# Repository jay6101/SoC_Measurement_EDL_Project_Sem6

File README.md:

# EE 344 EDL Project
Topic - SoC Measurement using Coulomb Counting Method

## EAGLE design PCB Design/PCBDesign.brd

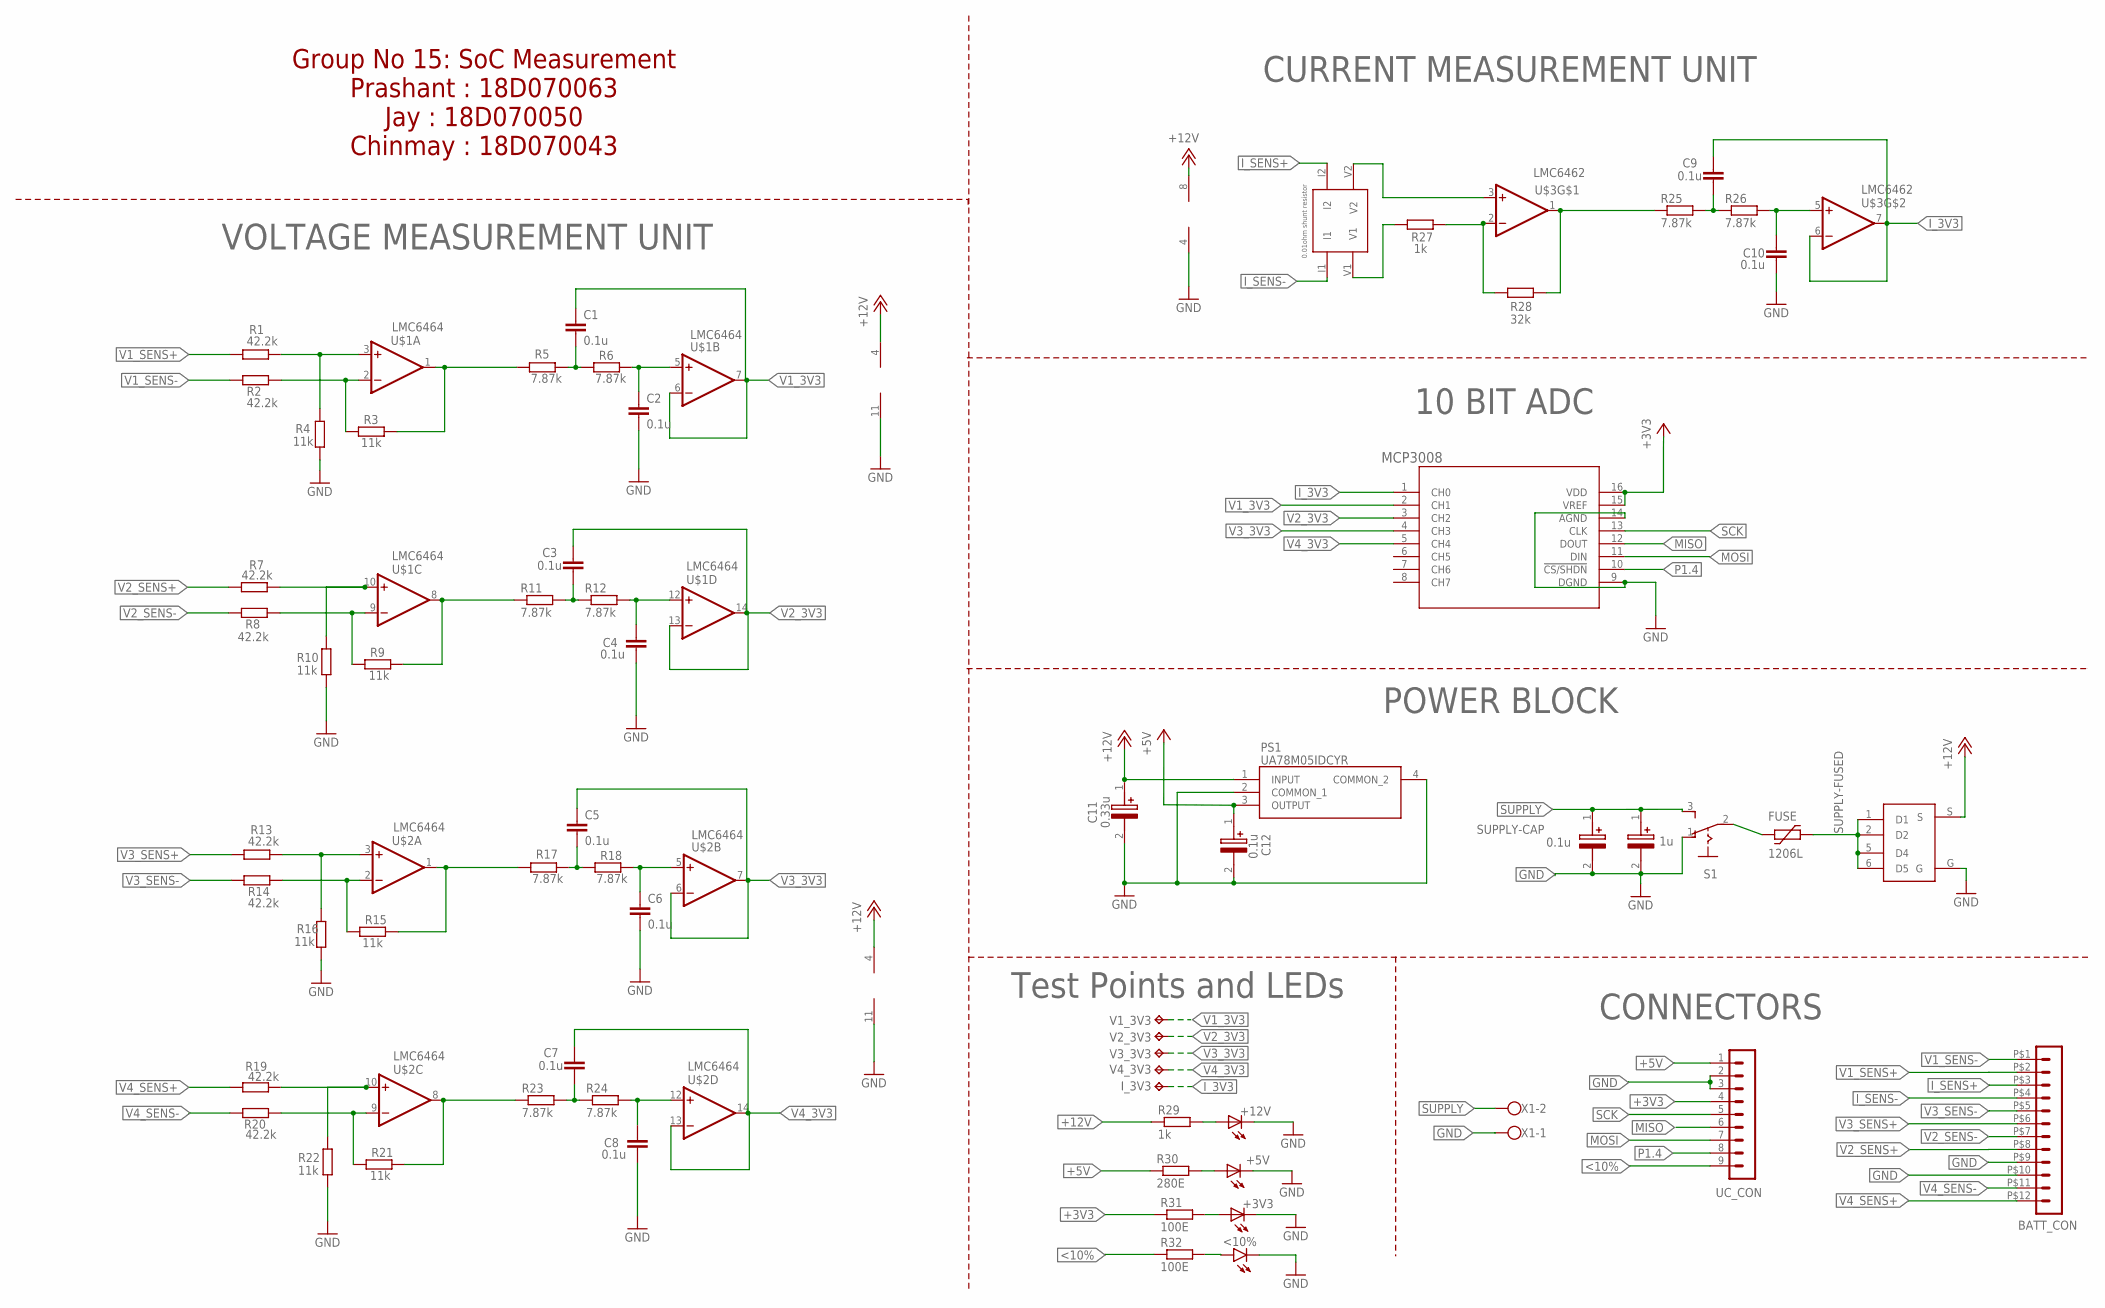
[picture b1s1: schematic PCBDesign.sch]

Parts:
+3V3, +5V, +12V: LED-FKIT-1206; FKIT-LED-1206
<10%: LED5MM
BATT_CON: HEADER_POS12_43045-1212; 43045-1212
C1, C2, C3, C4, C5, C6, C7, C8, C9, C10: 0.1u; C0805
C11: 0.33u; CAPPM2014X120N
C12: 0.1u; CAPPM2014X120N
FUSE: 1206L
I_3V3: TESTPADPAD1-13; P1-13
PS1: UA78M05IDCYR; SOT230P700X180-4N
R1, R2, R7, R8, R13, R14, R19, R20: 42.2k; R0805
R3, R4, R9, R10, R15, R16, R21, R22: 11k; R0805
R5, R6, R11, R12, R17, R18, R23, R24, R25, R26: 7.87k; R0805
R27, R29: 1k; R0805
R28: 32k; R0805
R30: 280E; R0805
R31, R32: 100E; R0805
S1: STS121PC04
S2: DMP3125L/SQ3419AEEV
SUPPLY-CAP: 1u; CAPPM2014X120N
SUPPLY-CAP1: 0.1u; CAPPM2014X120N
U1: MCP3008; SOIC16-N_MC_MCH-L
U$1, U$2: LMC6464; SO14_LONGPADS
U$3: LMC6462; S08
U$4: 0.01E; SHNT_R_0.01
UC_CON: MA09-1
V1_3V3, V2_3V3, V3_3V3, V4_3V3: TESTPADPAD1-13; P1-13
X1: W237-102

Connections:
+3V3: R31.1, U1.15 (VREF), U1.16 (VDD), UC_CON.4
+5V: C12.1 (+), PS1.3 (OUTPUT), R30.1, UC_CON.1
+12V: C11.1 (+), PS1.1 (INPUT), R29.1, S2.S, U$1.4 (V+), U$2.4 (V+), U$3.8 (V+)
<10%: R32.1, UC_CON.9
GND: +3V3.C, +5V.C, +12V.C, <10%.K (C), BATT_CON.P$9 (9), BATT_CON.P$10 (10), C2.2, C4.2, C6.2, C8.2, C10.2, C11.2 (-), C12.2 (-), PS1.2 (COMMON_1), PS1.4 (COMMON_2), R4.2, R10.2, R16.2, R22.2, S1.1 (O), S2.G, SUPPLY-CAP.2 (-), SUPPLY-CAP1.2 (-), U1.9 (DGND), U1.14 (AGND), U$1.11 (V-), U$2.11 (V-), U$3.4 (V-), UC_CON.2, UC_CON.3, X1.1
I_3V3: C9.1, I_3V3.TP, U1.1 (CH0), U$3.6 (-IN), U$3.7 (OUT)
I_SENS+: BATT_CON.P$3 (3), U$4.I2
I_SENS-: BATT_CON.P$4 (4), U$4.I1
MISO: U1.12 (DOUT), UC_CON.6
MOSI: U1.11 (DIN), UC_CON.7
unnamed: C1.2, R5.2, R6.1
unnamed: R1.2, R4.1, U$1.3 (+IN)
unnamed: R2.2, R3.1, U$1.2 (-IN)
unnamed: R3.2, R5.1, U$1.1 (OUT)
unnamed: FUSE.P$1 (1), S1.2
unnamed: +5V.A, R30.2
unnamed: C2.1, R6.2, U$1.5 (+IN)
unnamed: +3V3.A, R31.2
unnamed: R7.2, R10.1, U$1.10 (+IN)
unnamed: R8.2, R9.1, U$1.9 (-IN)
unnamed: <10%.A, R32.2
unnamed: R9.2, R11.1, U$1.8 (OUT)
unnamed: C3.2, R11.2, R12.1
unnamed: C5.2, R17.2, R18.1
unnamed: C4.1, R12.2, U$1.12 (+IN)
unnamed: +12V.A, R29.2
unnamed: R13.2, R16.1, U$2.3 (+IN)
unnamed: R14.2, R15.1, U$2.2 (-IN)
unnamed: R15.2, R17.1, U$2.1 (OUT)
unnamed: C6.1, R18.2, U$2.5 (+IN)
unnamed: R19.2, R22.1, U$2.10 (+IN)
unnamed: R20.2, R21.1, U$2.9 (-IN)
unnamed: R21.2, R23.1, U$2.8 (OUT)
unnamed: C7.2, R23.2, R24.1
unnamed: C8.1, R24.2, U$2.12 (+IN)
unnamed: R25.1, R28.2, U$3.1 (OUT)
unnamed: C9.2, R25.2, R26.1
unnamed: C10.1, R26.2, U$3.5 (+IN)
unnamed: R27.2, R28.1, U$3.2 (-IN)
unnamed: U$3.3 (+IN), U$4.V2
unnamed: R27.1, U$4.V1
P1.4: U1.10 (!CS/SHDN), UC_CON.8
SCK: U1.13 (CLK), UC_CON.5
SUPPLY: S1.3 (S), SUPPLY-CAP.1 (+), SUPPLY-CAP1.1 (+), X1.2
SUPPLY-FUSED: FUSE.P$2 (2), S2.1 (D1), S2.2 (D2), S2.5 (D4), S2.6 (D5)
V1_3V3: C1.1, U1.2 (CH1), U$1.6 (-IN), U$1.7 (OUT), V1_3V3.TP
V1_SENS+: BATT_CON.P$2 (2), R1.1
V1_SENS-: BATT_CON.P$1 (1), R2.1
V2_3V3: C3.1, U1.3 (CH2), U$1.13 (-IN), U$1.14 (OUT), V2_3V3.TP
V2_SENS+: BATT_CON.P$8 (8), R7.1
V2_SENS-: BATT_CON.P$7 (7), R8.1
V3_3V3: C5.1, U1.4 (CH3), U$2.6 (-IN), U$2.7 (OUT), V3_3V3.TP
V3_SENS+: BATT_CON.P$6 (6), R13.1
V3_SENS-: BATT_CON.P$5 (5), R14.1
V4_3V3: C7.1, U1.5 (CH4), U$2.13 (-IN), U$2.14 (OUT), V4_3V3.TP
V4_SENS+: BATT_CON.P$12 (12), R19.1
V4_SENS-: BATT_CON.P$11 (11), R20.1

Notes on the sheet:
VOLTAGE MEASUREMENT UNIT
CURRENT MEASUREMENT UNIT
10 BIT ADC
POWER BLOCK
CONNECTORS
Group No 15: SoC Measurement Prashant : 18D070063 Jay : 18D070050 Chinmay : 18D070043
0.01ohm shunt resistor
Test Points and LEDs

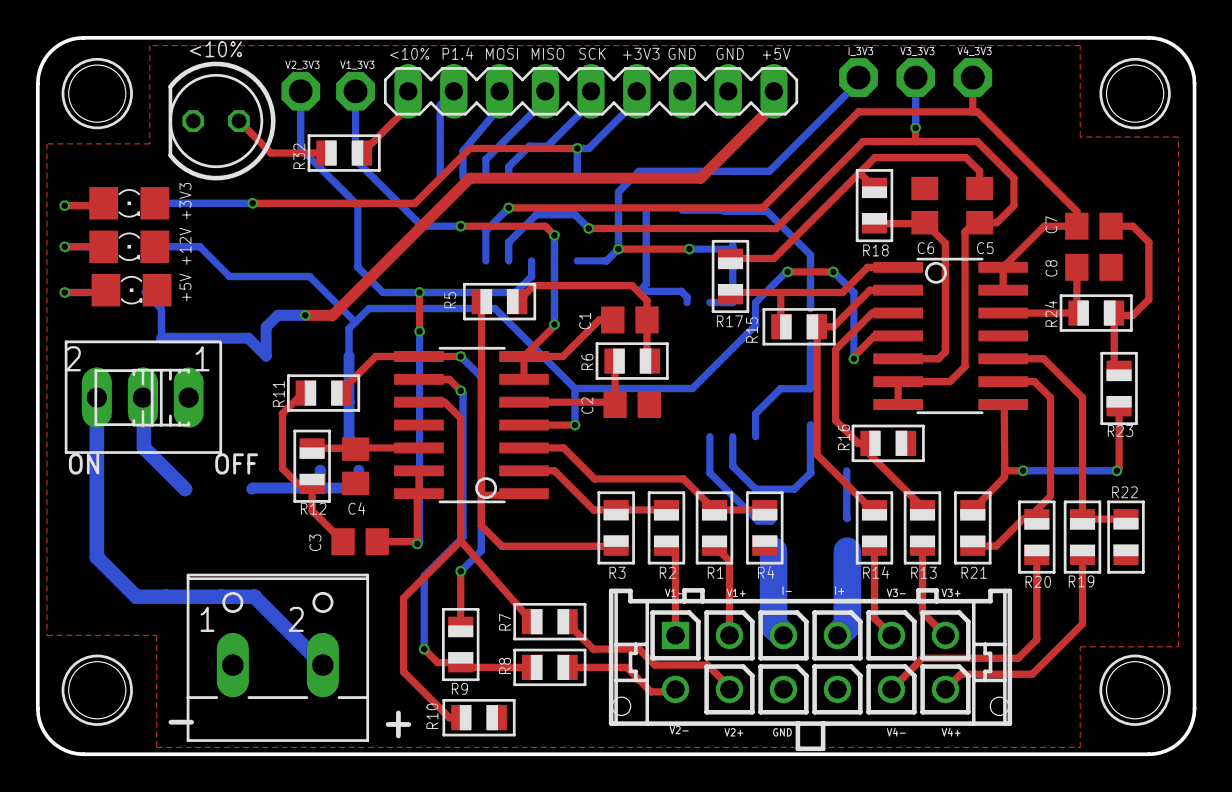
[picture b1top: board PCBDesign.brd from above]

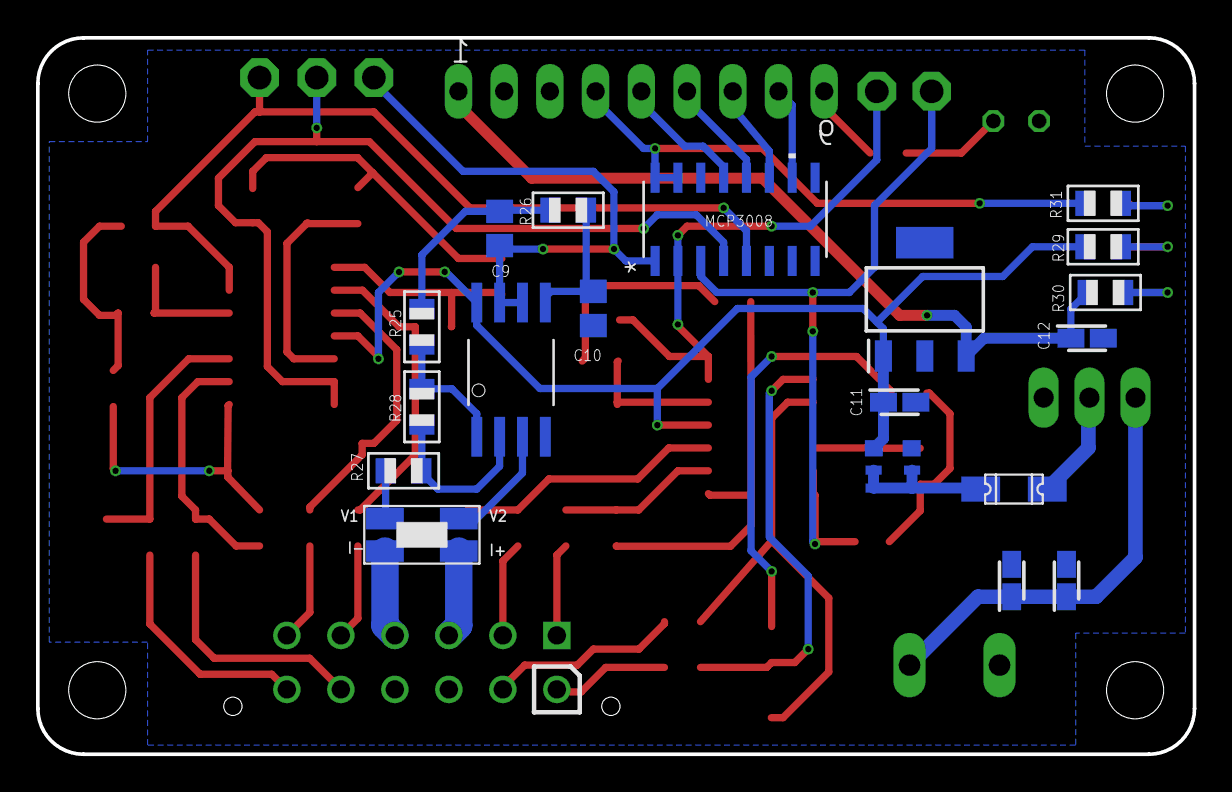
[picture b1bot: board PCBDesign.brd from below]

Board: 2 copper layers, 64.3 x 39.8 mm, 67 parts (19 on the bottom side), 57 nets.

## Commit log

2021-04-15 Adding the SOC over time datafile
    Committing and merging directly to the main branch.
2021-04-15 PCB Design
    This file contains .sch and .brd files

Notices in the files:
parts and their libraries:
COPYRIGHT: Copyright (C) 2018 Accelerated Designs. All rights reserved
